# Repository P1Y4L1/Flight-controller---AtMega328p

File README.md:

# Flight-controller---AtMega328p
PCB designs of a flight controller with the help of AtMega328p

Flight controls nowadays are costly and are too complex to operate for a beginner with drones. 
This makes operating the drone difficult and also we  consider the fact that we need to buy the expensive flight controller from the market. 
The significance of this paper is to show that we can make a basic flight controller back at home making it cheap and also quite basic to operate.
The 3 softwares used to make the PCB design of the Flight controller is Eagle Cad which is quite famous in the market however it is highly charged ;  
KiCad , a free and an open source software which is easily accessible and is beginner friendly ; last but not the least Fritzing , which is not commonly used by 
everyone , but is also open source but makes electronics accessible as a creative material for anyone.  With the help of these 3 softwares , it is shown that the 
PCB design of the Flight controller can be made in any software required and not necessarily in any of those 3 mentioned above.

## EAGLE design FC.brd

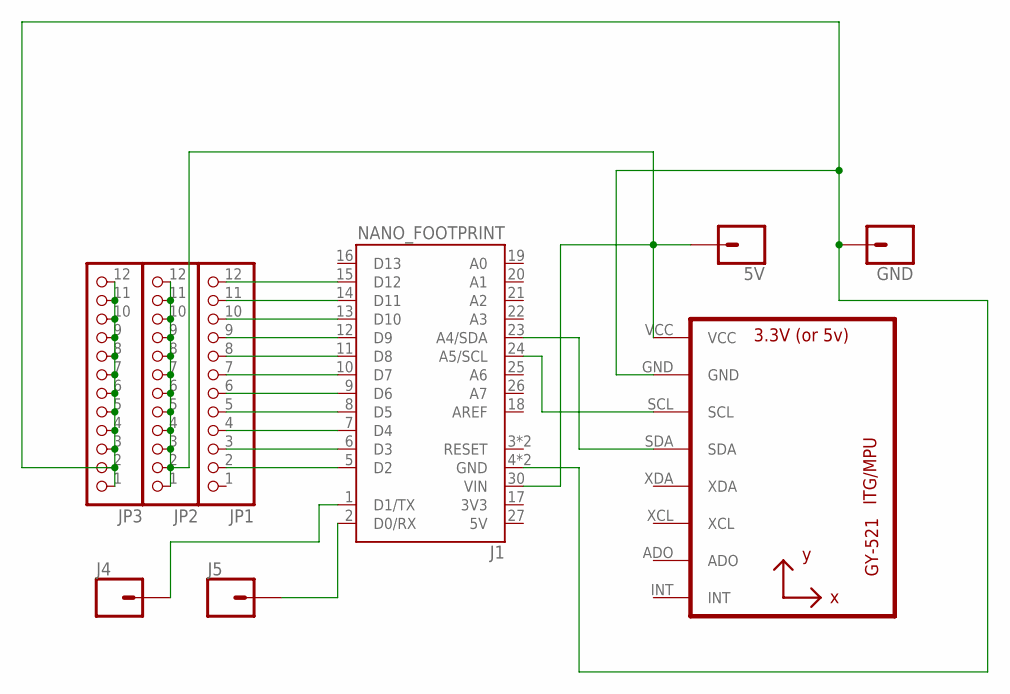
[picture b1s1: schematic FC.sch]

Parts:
5V: CONN_01PTH_NO_SILK_SMALL; 1X01_SMALL
GND: CONN_01PTH_NO_SILK_SMALL; 1X01_SMALL
J1: NANO_FOOTPRINT; NANO
J4, J5: CONN_01; 1X01
JP1, JP2, JP3: PINHD-1X12-CB; 1X12-CB
U1: GY-521MPU6050; GY-521

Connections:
unnamed: J1.24 (A5/SCL), U1.SCL
unnamed: J1.23 (A4/SDA), U1.SDA
unnamed: J1.6 (D3), JP1.3
unnamed: J1.7 (D4), JP1.4
unnamed: J1.9 (D6), JP1.6
unnamed: J1.10 (D7), JP1.7
unnamed: 5V.P$1, GND.P$1, J1.4 (GND), J1.5 (D2), J1.8 (D5), J1.29 (GND), J1.30 (VIN), JP1.2, JP1.5, JP2.1, JP2.2, JP2.3, JP2.4, JP2.5, JP2.6, JP2.7, JP2.8, JP2.9, JP2.10, JP2.11, JP2.12, JP3.1, JP3.2, JP3.3, JP3.4, JP3.5, JP3.6, JP3.7, JP3.8, JP3.9, JP3.10, JP3.11, JP3.12, U1.GND, U1.VCC
unnamed: J1.11 (D8), JP1.8
unnamed: J1.12 (D9), JP1.9
unnamed: J1.13 (D10), JP1.10
unnamed: J1.14 (D11), JP1.11
unnamed: J1.15 (D12), JP1.12
unnamed: J1.1 (D1/TX), J4.1
unnamed: J1.2 (D0/RX), J5.1

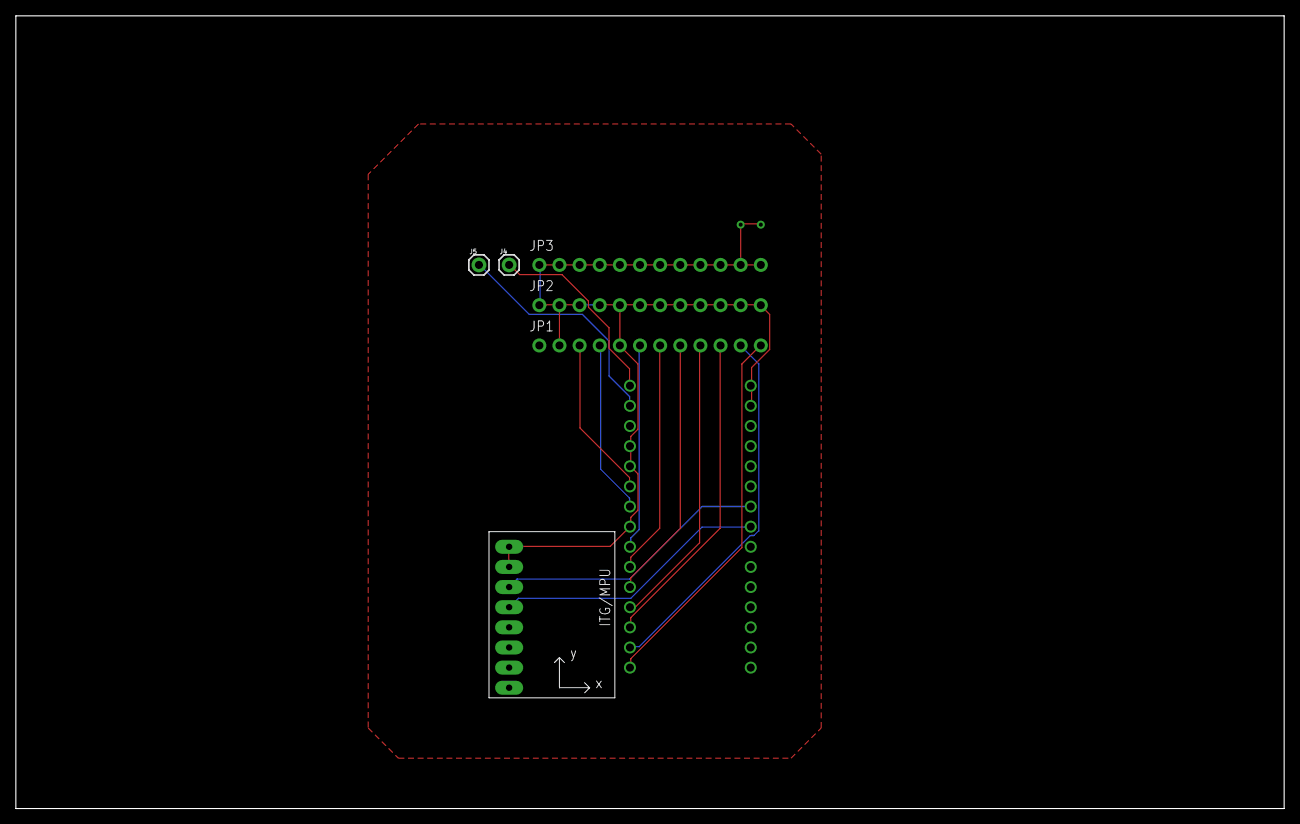
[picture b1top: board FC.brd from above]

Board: 2 copper layers, 160.0 x 100.0 mm, 9 parts (0 on the bottom side), 14 nets.

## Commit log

2021-02-18 PCB designs of a flight controller with the help of AtMega328p
    files uploaded of pro. ; sch. ; brd. file types

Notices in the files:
parts and their libraries:
SparkFun-Connectors: Licensing: Creative Commons ShareAlike 4.0 International - https://creativecommons.org/licenses/by-sa/4.0
